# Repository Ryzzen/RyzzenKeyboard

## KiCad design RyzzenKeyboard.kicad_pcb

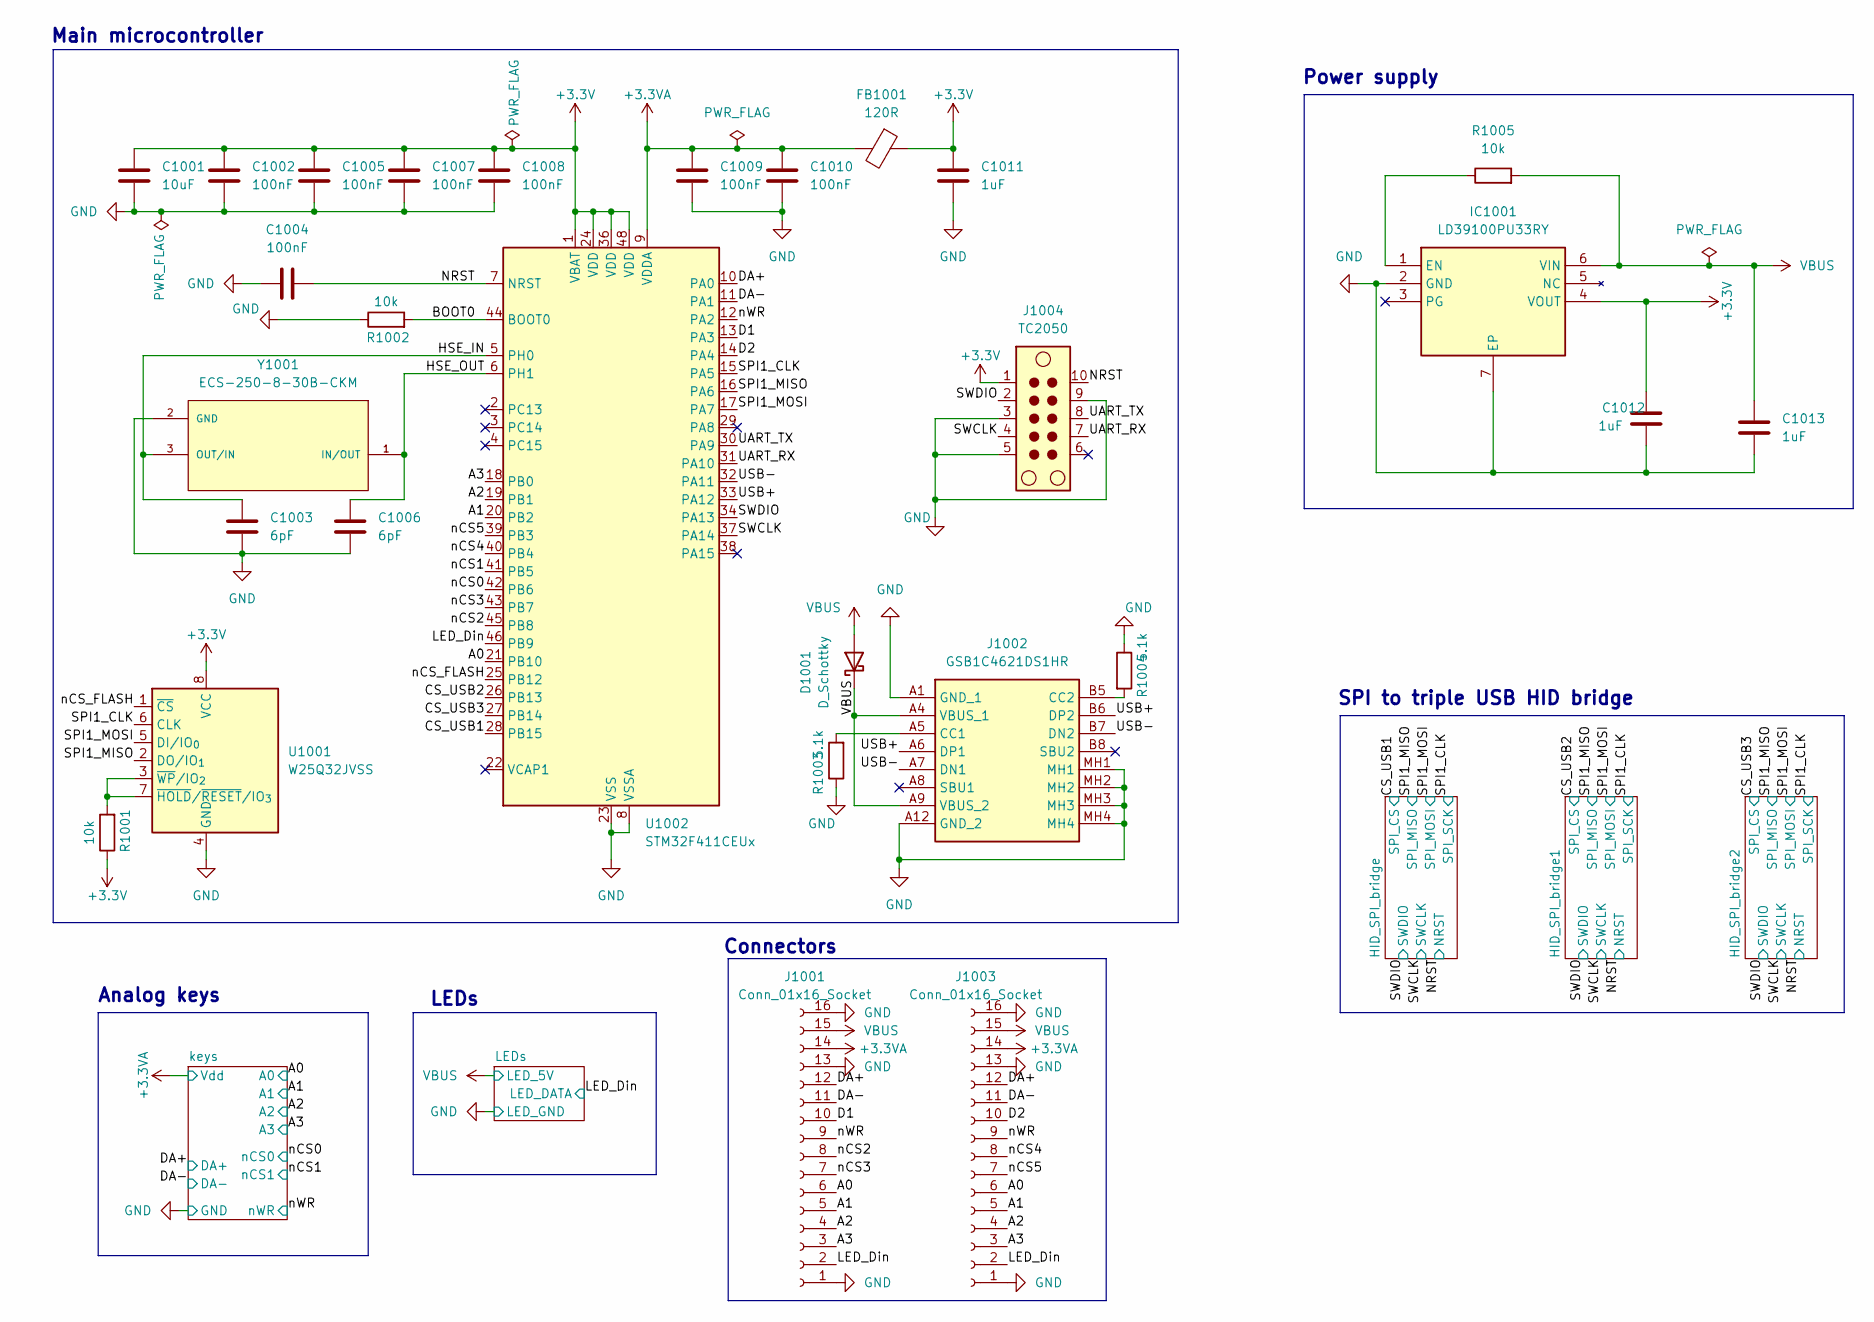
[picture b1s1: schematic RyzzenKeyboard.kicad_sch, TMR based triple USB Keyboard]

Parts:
C1001: 10uF; C_0603_1608Metric_Pad1.08x0.95mm_HandSolder
C1002, C1004, C1005, C1007, C1008, C1009, C1010: 100nF; C_0603_1608Metric_Pad1.08x0.95mm_HandSolder
C1003, C1006: 6pF; C_0603_1608Metric_Pad1.08x0.95mm_HandSolder
C1011, C1012, C1013: 1uF; C_0603_1608Metric_Pad1.08x0.95mm_HandSolder
D1001: D_Schottky; CUHS20S40H3F
FB1001: 120R; BLM21AG102BH1J
IC1001: LD39100PU33RY; SON95P300X300X90-7N-D; Mouser Part Number 511-LD39100PU33RY
J1001, J1003: Conn_01x16_Socket; JST_XH_S16B-XH-A_1x16_P2.50mm_Horizontal
J1002: GSB1C4621DS1HR; Manufacturer_Part_Number GSB1C4621DS1HR
J1004: TC2050; Tag-Connect_TC2050-IDC-NL_2x05_P1.27mm_Vertical
R1001, R1002, R1005: 10k; R_0603_1608Metric_Pad0.98x0.95mm_HandSolder
R1003, R1004: 5.1k; R_0603_1608Metric_Pad0.98x0.95mm_HandSolder
U1001: W25Q32JVSS; SOIC-8_5.3x5.3mm_P1.27mm
U1002: STM32F411CEUx; QFN-48-1EP_7x7mm_P0.5mm_EP5.6x5.6mm
Y1001: ECS-250-8-30B-CKM; XTAL_ECS-250-8-30B-CKM

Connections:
+3.3V: C1001.1, C1002.1, C1005.1, C1007.1, C1008.1, C1011.1, C1012.1, FB1001.1, IC1001.4 (VOUT), J1004.1, R1001.1, U1001.8 (VCC), U1002.1 (VBAT), U1002.24 (VDD), U1002.36 (VDD), U1002.48 (VDD); also elsewhere on the board
+3.3VA: C1009.1, C1010.1, FB1001.2, J1001.14, J1003.14, U1002.9 (VDDA); also elsewhere on the board
/A0: J1001.6, J1003.6, U1002.21 (PB10); also elsewhere on the board
/A1: J1001.5, J1003.5, U1002.20 (PB2); also elsewhere on the board
/A2: J1001.4, J1003.4, U1002.19 (PB1); also elsewhere on the board
/A3: J1001.3, J1003.3, U1002.18 (PB0); also elsewhere on the board
/BOOT0: R1002.2, U1002.44 (BOOT0)
/CS_USB1: U1002.28 (PB15); also elsewhere on the board
/CS_USB2: U1002.26 (PB13); also elsewhere on the board
/CS_USB3: U1002.27 (PB14); also elsewhere on the board
/D1: J1001.10, U1002.13 (PA3)
/D2: J1003.10, U1002.14 (PA4)
/DA+: J1001.12, J1003.12, U1002.10 (PA0); also elsewhere on the board
/DA-: J1001.11, J1003.11, U1002.11 (PA1); also elsewhere on the board
/HSE_IN: C1003.1, U1002.5 (PH0), Y1001.3 (OUT/IN)
/HSE_OUT: C1006.1, U1002.6 (PH1), Y1001.1 (IN/OUT)
/LED_Din: J1001.2, J1003.2, U1002.46 (PB9); also elsewhere on the board
/NRST: C1004.1, J1004.10, U1002.7 (NRST); also elsewhere on the board
/SPI1_CLK: U1001.6 (CLK), U1002.15 (PA5); also elsewhere on the board
/SPI1_MISO: U1001.2 (DO/IO_{1}), U1002.16 (PA6); also elsewhere on the board
/SPI1_MOSI: U1001.5 (DI/IO_{0}), U1002.17 (PA7); also elsewhere on the board
/SWCLK: J1004.4, U1002.37 (PA14); also elsewhere on the board
/SWDIO: J1004.2, U1002.34 (PA13); also elsewhere on the board
/UART_RX: J1004.7, U1002.31 (PA10)
/UART_TX: J1004.8, U1002.30 (PA9)
/USB+: J1002.A6 (DP1), J1002.B6 (DP2), U1002.33 (PA12)
/USB-: J1002.A7 (DN1), J1002.B7 (DN2), U1002.32 (PA11)
/nCS0: U1002.42 (PB6); also elsewhere on the board
/nCS1: U1002.41 (PB5); also elsewhere on the board
/nCS2: J1001.8, U1002.45 (PB8)
/nCS3: J1001.7, U1002.43 (PB7)
/nCS4: J1003.8, U1002.40 (PB4)
/nCS5: J1003.7, U1002.39 (PB3)
/nCS_FLASH: U1001.1 (~CS), U1002.25 (PB12)
/nWR: J1001.9, J1003.9, U1002.12 (PA2); also elsewhere on the board
GND: C1001.2, C1002.2, C1003.2, C1004.2, C1005.2, C1006.2, C1007.2, C1008.2, C1009.2, C1010.2, C1011.2, C1012.2, C1013.2, IC1001.2 (GND), IC1001.7 (EP), J1001.1, J1001.13, J1001.16, J1002.A1 (GND_1), J1002.A12 (GND_2), J1002.MH1, J1002.MH2, J1002.MH3, J1002.MH4, J1003.1, J1003.13, J1003.16, J1004.3, J1004.5, J1004.9, R1002.1, R1003.1, R1004.1, U1001.4 (GND), U1002.8 (VSSA), U1002.23 (VSS), U1002.35 (VSS), U1002.47 (VSS), U1002.49 (VSS), Y1001.2 (GND), Y1001.4 (GND); also elsewhere on the board
unnamed: IC1001.1 (EN), R1005.1
unnamed: J1002.A5 (CC1), R1003.2
unnamed: J1002.B5 (CC2), R1004.2
unnamed: R1001.2, U1001.3 (~WP/IO_{2}), U1001.7 (~HOLD/~RESET/IO_{3})
VBUS: C1013.1, D1001.1 (K), D1001.2 (A), IC1001.6 (VIN), J1001.15, J1002.A4 (VBUS_1), J1002.A9 (VBUS_2), J1003.15, R1005.2; also elsewhere on the board

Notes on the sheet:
Main microcontroller
Power supply
LEDs
Connectors
Analog keys
SPI to triple USB HID bridge

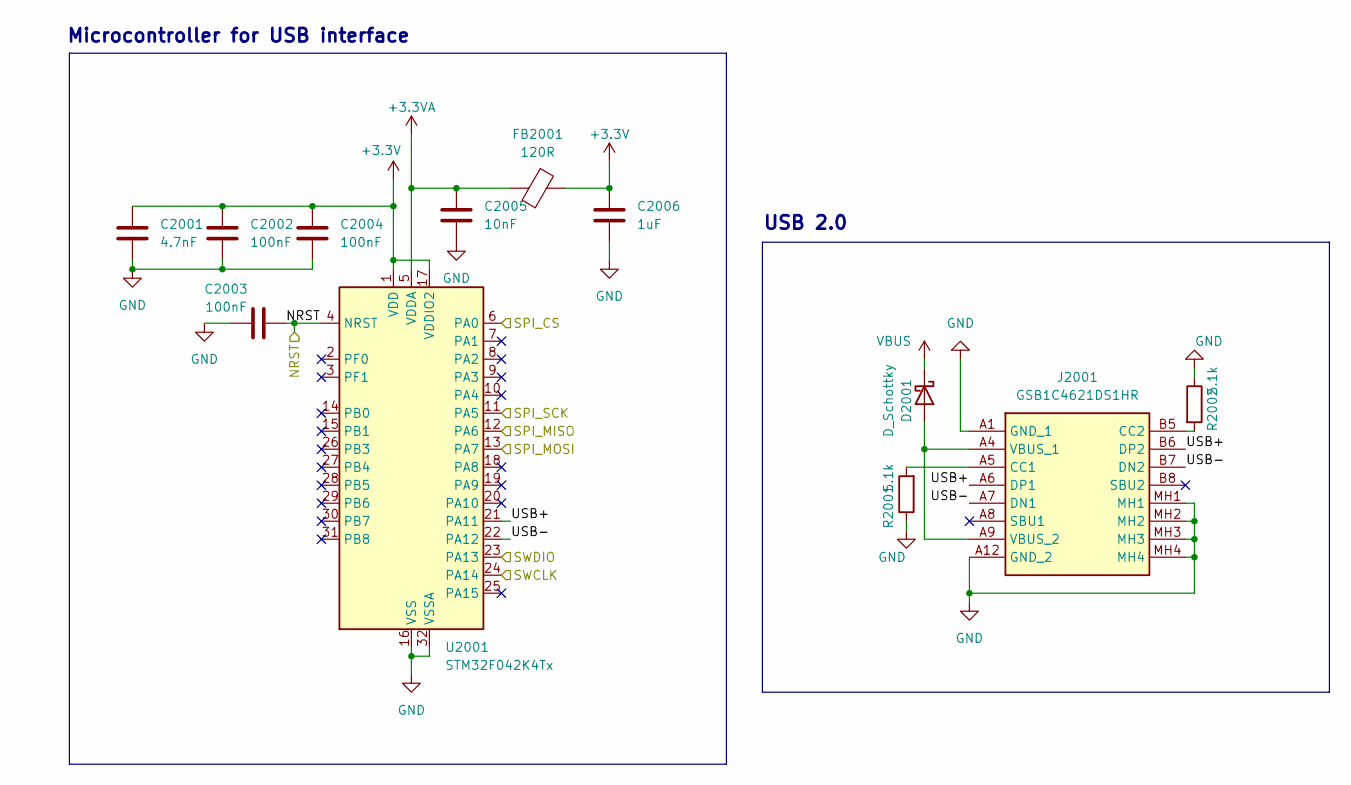
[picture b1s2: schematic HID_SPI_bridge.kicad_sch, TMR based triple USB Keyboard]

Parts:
C2001: 4.7nF; C_0603_1608Metric_Pad1.08x0.95mm_HandSolder
C2002, C2003, C2004: 100nF; C_0603_1608Metric_Pad1.08x0.95mm_HandSolder
C2005: 10nF; C_0603_1608Metric_Pad1.08x0.95mm_HandSolder
C2006: 1uF; C_0603_1608Metric_Pad1.08x0.95mm_HandSolder
D2001: D_Schottky; CUHS20S40H3F
FB2001: 120R; BLM21AG102BH1J
J2001: GSB1C4621DS1HR; Manufacturer_Part_Number GSB1C4621DS1HR
R2001, R2002: 5.1k; R_0603_1608Metric_Pad0.98x0.95mm_HandSolder
U2001: STM32F042K4Tx; LQFP-32_7x7mm_P0.8mm

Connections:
+3.3V: C2001.1, C2002.1, C2004.1, C2006.1, FB2001.1, U2001.1 (VDD), U2001.17 (VDDIO2); also elsewhere on the board
+3.3VA: C2005.1, FB2001.2, U2001.5 (VDDA); also elsewhere on the board
/CS_USB1: U2001.6 (PA0); also elsewhere on the board
/HID_SPI_bridge/USB+: J2001.A6 (DP1), J2001.B6 (DP2), U2001.21 (PA11)
/HID_SPI_bridge/USB-: J2001.A7 (DN1), J2001.B7 (DN2), U2001.22 (PA12)
/NRST: C2003.2, U2001.4 (NRST); also elsewhere on the board
/SPI1_CLK: U2001.11 (PA5); also elsewhere on the board
/SPI1_MISO: U2001.12 (PA6); also elsewhere on the board
/SPI1_MOSI: U2001.13 (PA7); also elsewhere on the board
/SWCLK: U2001.24 (PA14); also elsewhere on the board
/SWDIO: U2001.23 (PA13); also elsewhere on the board
GND: C2001.2, C2002.2, C2003.1, C2004.2, C2005.2, C2006.2, J2001.A1 (GND_1), J2001.A12 (GND_2), J2001.MH1, J2001.MH2, J2001.MH3, J2001.MH4, R2001.1, R2002.1, U2001.16 (VSS), U2001.32 (VSSA); also elsewhere on the board
unnamed: D2001.2 (A), J2001.A4 (VBUS_1), J2001.A9 (VBUS_2)
unnamed: J2001.A5 (CC1), R2001.2
unnamed: J2001.B5 (CC2), R2002.2
VBUS: D2001.1 (K); also elsewhere on the board

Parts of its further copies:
C207001, C208001: 4.7nF; C_0603_1608Metric_Pad1.08x0.95mm_HandSolder
C207002, C207003, C207004, C208002, C208003, C208004: 100nF; C_0603_1608Metric_Pad1.08x0.95mm_HandSolder
C207005, C208005: 10nF; C_0603_1608Metric_Pad1.08x0.95mm_HandSolder
C207006, C208006: 1uF; C_0603_1608Metric_Pad1.08x0.95mm_HandSolder
D207001, D208001: D_Schottky; CUHS20S40H3F
FB207001, FB208001: 120R; BLM21AG102BH1J
J207001, J208001: GSB1C4621DS1HR; Manufacturer_Part_Number GSB1C4621DS1HR
R207001, R207002, R208001, R208002: 5.1k; R_0603_1608Metric_Pad0.98x0.95mm_HandSolder
U207001, U208001: STM32F042K4Tx; LQFP-32_7x7mm_P0.8mm

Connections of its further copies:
+3.3V: C207001.1, C207002.1, C207004.1, C207006.1, C208001.1, C208002.1, C208004.1, C208006.1, FB207001.1, FB208001.1, U207001.1 (VDD), U207001.17 (VDDIO2), U208001.1 (VDD), U208001.17 (VDDIO2); also elsewhere on the board
+3.3VA: C207005.1, C208005.1, FB207001.2, FB208001.2, U207001.5 (VDDA), U208001.5 (VDDA); also elsewhere on the board
/CS_USB2: U208001.6 (PA0); also elsewhere on the board
/CS_USB3: U207001.6 (PA0); also elsewhere on the board
/HID_SPI_bridge1/USB+: J208001.A6 (DP1), J208001.B6 (DP2), U208001.21 (PA11)
/HID_SPI_bridge1/USB-: J208001.A7 (DN1), J208001.B7 (DN2), U208001.22 (PA12)
/HID_SPI_bridge2/USB+: J207001.A6 (DP1), J207001.B6 (DP2), U207001.21 (PA11)
/HID_SPI_bridge2/USB-: J207001.A7 (DN1), J207001.B7 (DN2), U207001.22 (PA12)
/NRST: C207003.2, C208003.2, U207001.4 (NRST), U208001.4 (NRST); also elsewhere on the board
/SPI1_CLK: U207001.11 (PA5), U208001.11 (PA5); also elsewhere on the board
/SPI1_MISO: U207001.12 (PA6), U208001.12 (PA6); also elsewhere on the board
/SPI1_MOSI: U207001.13 (PA7), U208001.13 (PA7); also elsewhere on the board
/SWCLK: U207001.24 (PA14), U208001.24 (PA14); also elsewhere on the board
/SWDIO: U207001.23 (PA13), U208001.23 (PA13); also elsewhere on the board
GND: C207001.2, C207002.2, C207003.1, C207004.2, C207005.2, C207006.2, C208001.2, C208002.2, C208003.1, C208004.2, C208005.2, C208006.2, J207001.A1 (GND_1), J207001.A12 (GND_2), J207001.MH1, J207001.MH2, J207001.MH3, J207001.MH4, J208001.A1 (GND_1), J208001.A12 (GND_2), J208001.MH1, J208001.MH2, J208001.MH3, J208001.MH4, R207001.1, R207002.1, R208001.1, R208002.1, U207001.16 (VSS), U207001.32 (VSSA), U208001.16 (VSS), U208001.32 (VSSA); also elsewhere on the board
unnamed: D207001.2 (A), J207001.A4 (VBUS_1), J207001.A9 (VBUS_2)
unnamed: D208001.2 (A), J208001.A4 (VBUS_1), J208001.A9 (VBUS_2)
unnamed: J207001.A5 (CC1), R207001.2
unnamed: J207001.B5 (CC2), R207002.2
unnamed: J208001.A5 (CC1), R208001.2
unnamed: J208001.B5 (CC2), R208002.2
VBUS: D207001.1 (K), D208001.1 (K); also elsewhere on the board

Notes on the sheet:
Microcontroller for USB interface
USB 2.0

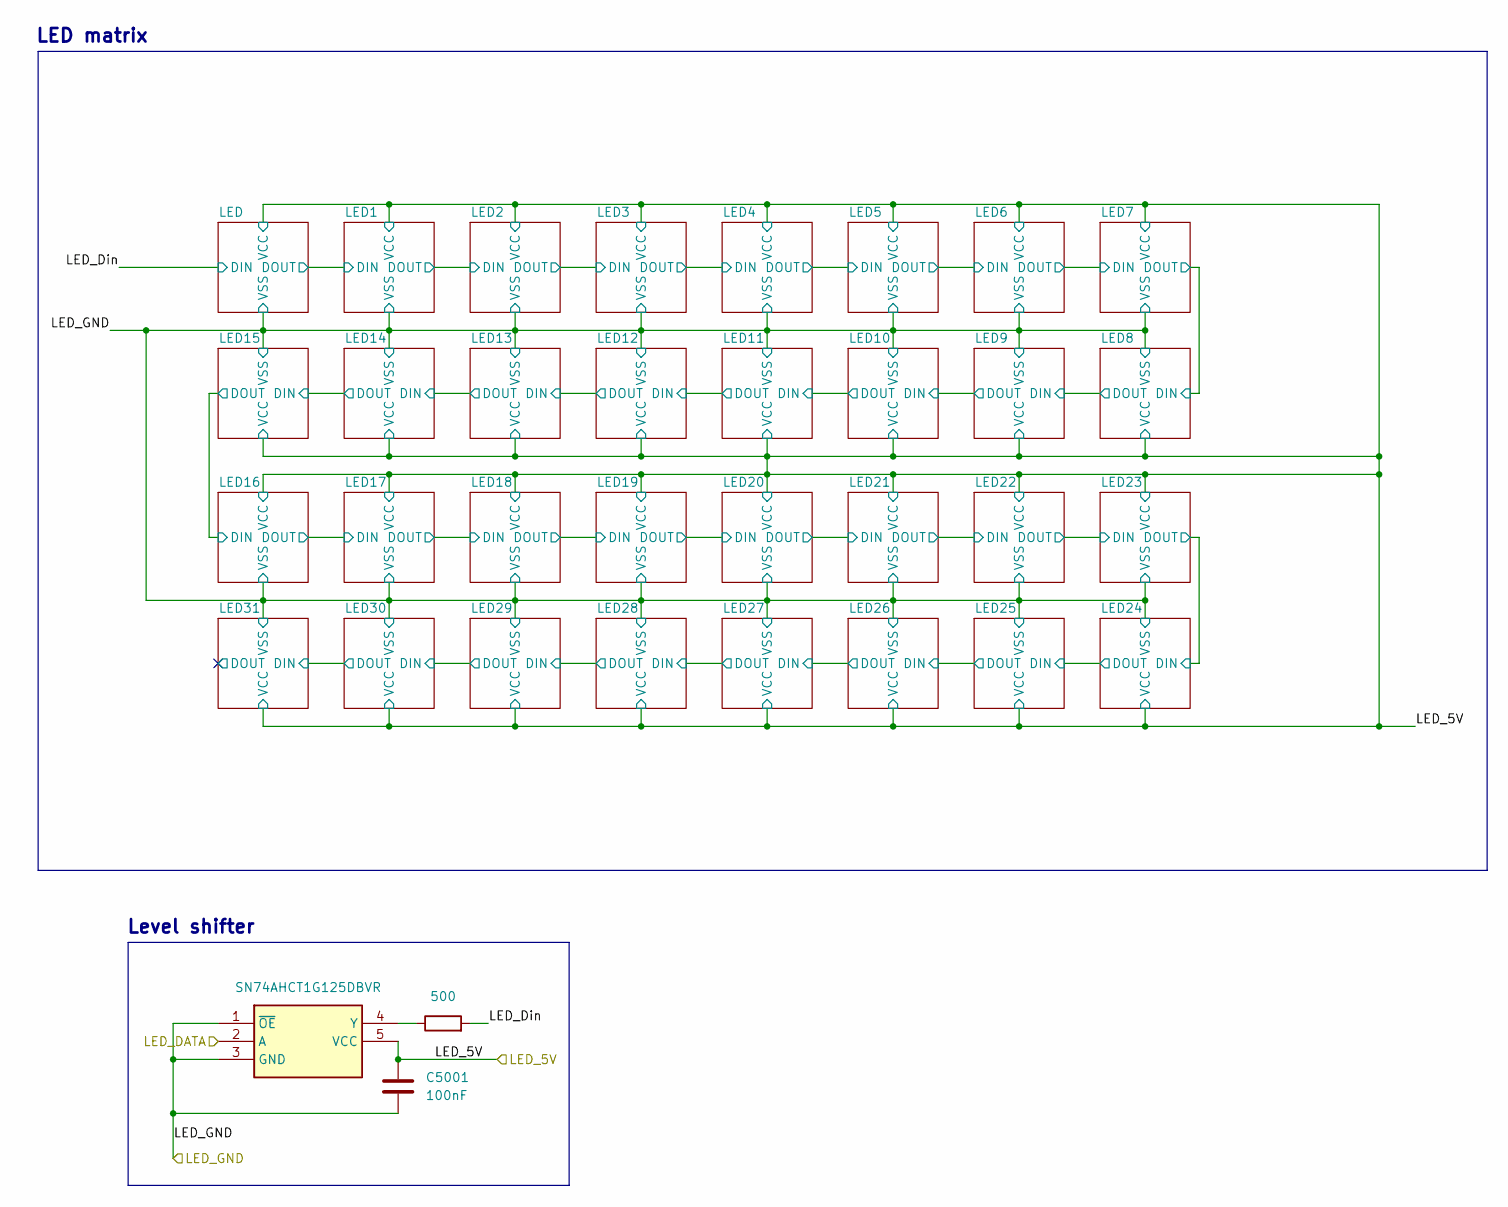
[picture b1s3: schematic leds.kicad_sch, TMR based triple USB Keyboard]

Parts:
C5001: 100nF; C_0603_1608Metric_Pad1.08x0.95mm_HandSolder
IC5001: SN74AHCT1G125DBVR; SOT95P280X145-5N; Mouser Part Number 595-SNAHCT1G125DBVR
R5001: 500; R_0603_1608Metric_Pad0.98x0.95mm_HandSolder

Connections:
/LED_Din: IC5001.2 (A); also elsewhere on the board
/LEDs/LED_Din: R5001.2; also elsewhere on the board
GND: C5001.1, IC5001.1 (~OE), IC5001.3 (GND); also elsewhere on the board
unnamed: IC5001.4 (Y), R5001.1
VBUS: C5001.2, IC5001.5 (VCC); also elsewhere on the board

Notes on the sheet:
LED matrix
Level shifter

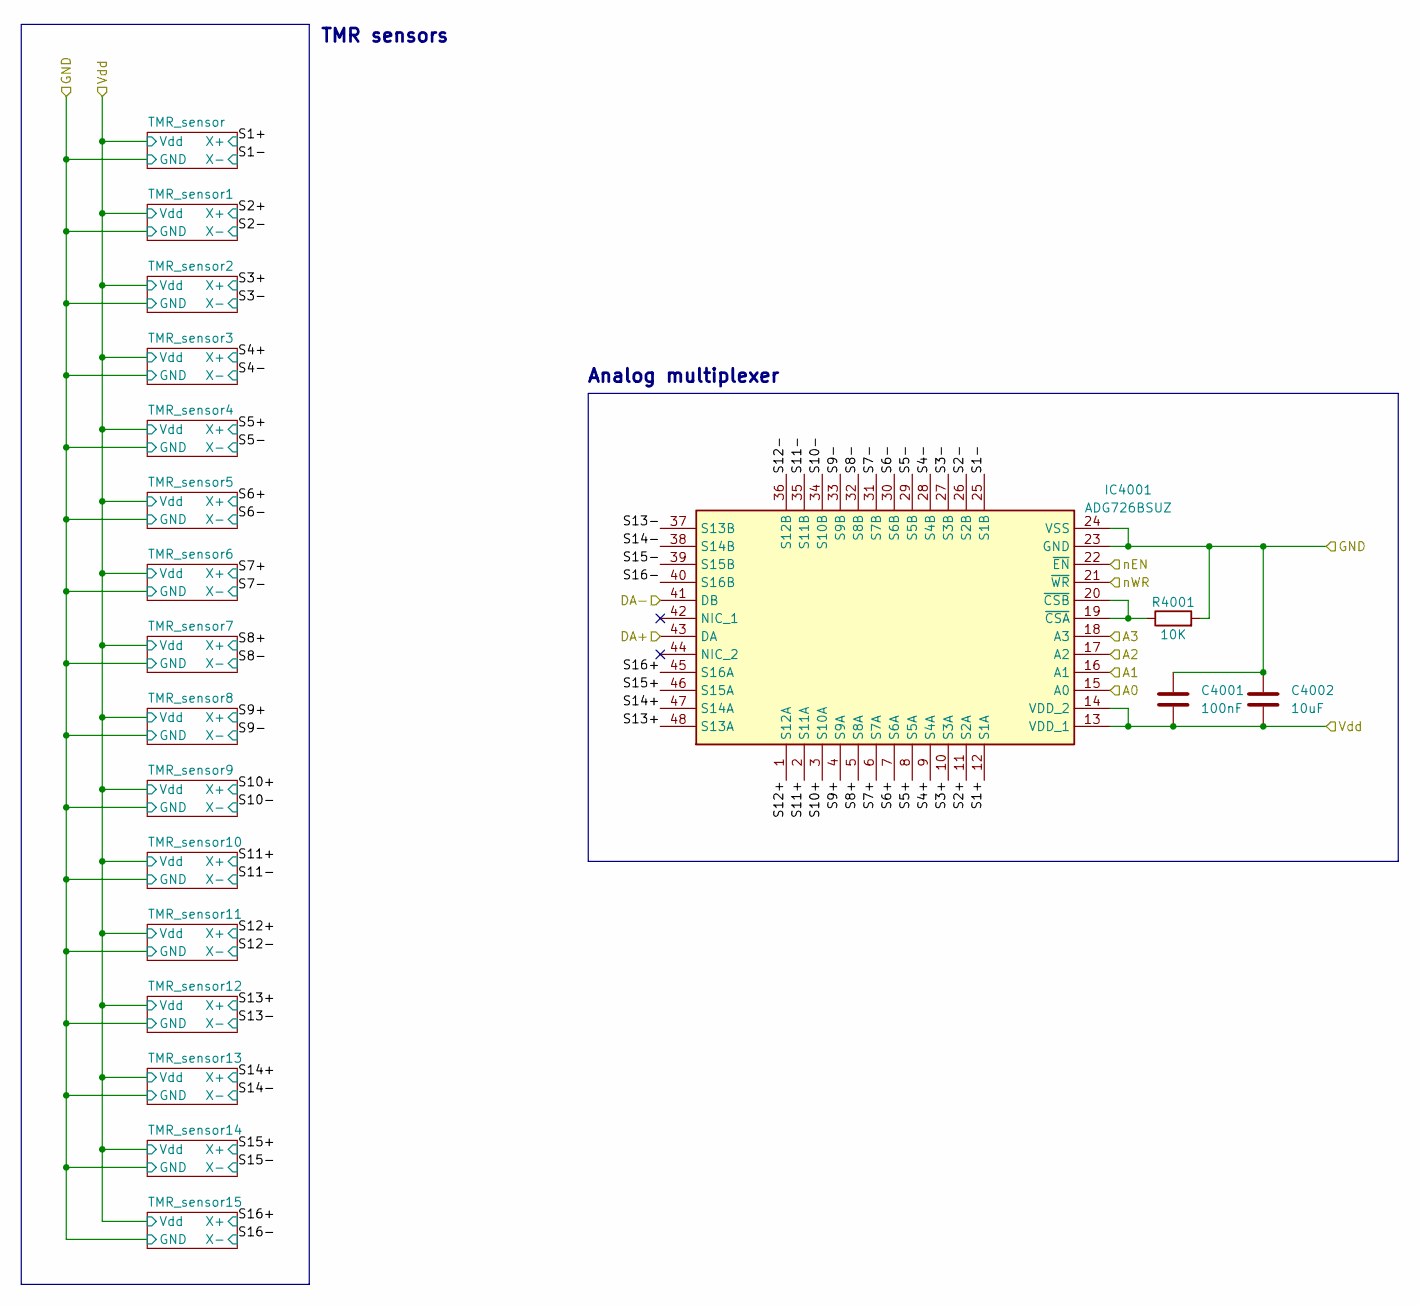
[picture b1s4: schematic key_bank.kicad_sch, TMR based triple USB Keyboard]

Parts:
C4001: 100nF; C_0603_1608Metric_Pad1.08x0.95mm_HandSolder
C4002: 10uF; C_0603_1608Metric_Pad1.08x0.95mm_HandSolder
IC4001: ADG726BSUZ; QFP50P900X900X120-48N; Mouser Part Number 584-ADG726BSUZ
R4001: 10K; R_0603_1608Metric_Pad0.98x0.95mm_HandSolder

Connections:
+3.3VA: C4001.2, C4002.2, IC4001.13 (VDD_1), IC4001.14 (VDD_2); also elsewhere on the board
/A0: IC4001.15 (A0); also elsewhere on the board
/A1: IC4001.16 (A1); also elsewhere on the board
/A2: IC4001.17 (A2); also elsewhere on the board
/A3: IC4001.18 (A3); also elsewhere on the board
/DA+: IC4001.43 (DA); also elsewhere on the board
/DA-: IC4001.41 (DB); also elsewhere on the board
/keys/key_bank2/S1+: IC4001.12 (S1A); also elsewhere on the board
/keys/key_bank2/S1-: IC4001.25 (S1B); also elsewhere on the board
/keys/key_bank2/S2+: IC4001.11 (S2A); also elsewhere on the board
/keys/key_bank2/S2-: IC4001.26 (S2B); also elsewhere on the board
/keys/key_bank2/S3+: IC4001.10 (S3A); also elsewhere on the board
/keys/key_bank2/S3-: IC4001.27 (S3B); also elsewhere on the board
/keys/key_bank2/S4+: IC4001.9 (S4A); also elsewhere on the board
/keys/key_bank2/S4-: IC4001.28 (S4B); also elsewhere on the board
/keys/key_bank2/S5+: IC4001.8 (S5A); also elsewhere on the board
/keys/key_bank2/S5-: IC4001.29 (S5B); also elsewhere on the board
/keys/key_bank2/S6+: IC4001.7 (S6A); also elsewhere on the board
/keys/key_bank2/S6-: IC4001.30 (S6B); also elsewhere on the board
/keys/key_bank2/S7+: IC4001.6 (S7A); also elsewhere on the board
/keys/key_bank2/S7-: IC4001.31 (S7B); also elsewhere on the board
/keys/key_bank2/S8+: IC4001.5 (S8A); also elsewhere on the board
/keys/key_bank2/S8-: IC4001.32 (S8B); also elsewhere on the board
/keys/key_bank2/S9+: IC4001.4 (S9A); also elsewhere on the board
/keys/key_bank2/S9-: IC4001.33 (S9B); also elsewhere on the board
/keys/key_bank2/S10+: IC4001.3 (S10A); also elsewhere on the board
/keys/key_bank2/S10-: IC4001.34 (S10B); also elsewhere on the board
/keys/key_bank2/S11+: IC4001.2 (S11A); also elsewhere on the board
/keys/key_bank2/S11-: IC4001.35 (S11B); also elsewhere on the board
/keys/key_bank2/S12+: IC4001.1 (S12A); also elsewhere on the board
/keys/key_bank2/S12-: IC4001.36 (S12B); also elsewhere on the board
/keys/key_bank2/S13+: IC4001.48 (S13A); also elsewhere on the board
/keys/key_bank2/S13-: IC4001.37 (S13B); also elsewhere on the board
/keys/key_bank2/S14+: IC4001.47 (S14A); also elsewhere on the board
/keys/key_bank2/S14-: IC4001.38 (S14B); also elsewhere on the board
/keys/key_bank2/S15+: IC4001.46 (S15A); also elsewhere on the board
/keys/key_bank2/S15-: IC4001.39 (S15B); also elsewhere on the board
/keys/key_bank2/S16+: IC4001.45 (S16A); also elsewhere on the board
/keys/key_bank2/S16-: IC4001.40 (S16B); also elsewhere on the board
/nCS0: IC4001.22 (~EN); also elsewhere on the board
/nWR: IC4001.21 (~WR); also elsewhere on the board
GND: C4001.1, C4002.1, IC4001.23 (GND), IC4001.24 (VSS), R4001.2; also elsewhere on the board
unnamed: IC4001.19 (~CSA), IC4001.20 (~CSB), R4001.1

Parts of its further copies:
C204001: 100nF; C_0603_1608Metric_Pad1.08x0.95mm_HandSolder
C204002: 10uF; C_0603_1608Metric_Pad1.08x0.95mm_HandSolder
IC204001: ADG726BSUZ; QFP50P900X900X120-48N; Mouser Part Number 584-ADG726BSUZ
R204001: 10K; R_0603_1608Metric_Pad0.98x0.95mm_HandSolder

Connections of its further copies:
+3.3VA: C204001.2, C204002.2, IC204001.13 (VDD_1), IC204001.14 (VDD_2); also elsewhere on the board
/A0: IC204001.15 (A0); also elsewhere on the board
/A1: IC204001.16 (A1); also elsewhere on the board
/A2: IC204001.17 (A2); also elsewhere on the board
/A3: IC204001.18 (A3); also elsewhere on the board
/DA+: IC204001.43 (DA); also elsewhere on the board
/DA-: IC204001.41 (DB); also elsewhere on the board
/keys/key_bank3/S1+: IC204001.12 (S1A); also elsewhere on the board
/keys/key_bank3/S1-: IC204001.25 (S1B); also elsewhere on the board
/keys/key_bank3/S2+: IC204001.11 (S2A); also elsewhere on the board
/keys/key_bank3/S2-: IC204001.26 (S2B); also elsewhere on the board
/keys/key_bank3/S3+: IC204001.10 (S3A); also elsewhere on the board
/keys/key_bank3/S3-: IC204001.27 (S3B); also elsewhere on the board
/keys/key_bank3/S4+: IC204001.9 (S4A); also elsewhere on the board
/keys/key_bank3/S4-: IC204001.28 (S4B); also elsewhere on the board
/keys/key_bank3/S5+: IC204001.8 (S5A); also elsewhere on the board
/keys/key_bank3/S5-: IC204001.29 (S5B); also elsewhere on the board
/keys/key_bank3/S6+: IC204001.7 (S6A); also elsewhere on the board
/keys/key_bank3/S6-: IC204001.30 (S6B); also elsewhere on the board
/keys/key_bank3/S7+: IC204001.6 (S7A); also elsewhere on the board
/keys/key_bank3/S7-: IC204001.31 (S7B); also elsewhere on the board
/keys/key_bank3/S8+: IC204001.5 (S8A); also elsewhere on the board
/keys/key_bank3/S8-: IC204001.32 (S8B); also elsewhere on the board
/keys/key_bank3/S9+: IC204001.4 (S9A); also elsewhere on the board
/keys/key_bank3/S9-: IC204001.33 (S9B); also elsewhere on the board
/keys/key_bank3/S10+: IC204001.3 (S10A); also elsewhere on the board
/keys/key_bank3/S10-: IC204001.34 (S10B); also elsewhere on the board
/keys/key_bank3/S11+: IC204001.2 (S11A); also elsewhere on the board
/keys/key_bank3/S11-: IC204001.35 (S11B); also elsewhere on the board
/keys/key_bank3/S12+: IC204001.1 (S12A); also elsewhere on the board
/keys/key_bank3/S12-: IC204001.36 (S12B); also elsewhere on the board
/keys/key_bank3/S13+: IC204001.48 (S13A); also elsewhere on the board
/keys/key_bank3/S13-: IC204001.37 (S13B); also elsewhere on the board
/keys/key_bank3/S14+: IC204001.47 (S14A); also elsewhere on the board
/keys/key_bank3/S14-: IC204001.38 (S14B); also elsewhere on the board
/keys/key_bank3/S15+: IC204001.46 (S15A); also elsewhere on the board
/keys/key_bank3/S15-: IC204001.39 (S15B); also elsewhere on the board
/keys/key_bank3/S16+: IC204001.45 (S16A); also elsewhere on the board
/keys/key_bank3/S16-: IC204001.40 (S16B); also elsewhere on the board
/nCS1: IC204001.22 (~EN); also elsewhere on the board
/nWR: IC204001.21 (~WR); also elsewhere on the board
GND: C204001.1, C204002.1, IC204001.23 (GND), IC204001.24 (VSS), R204001.2; also elsewhere on the board
unnamed: IC204001.19 (~CSA), IC204001.20 (~CSB), R204001.1

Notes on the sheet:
TMR sensors
Analog multiplexer

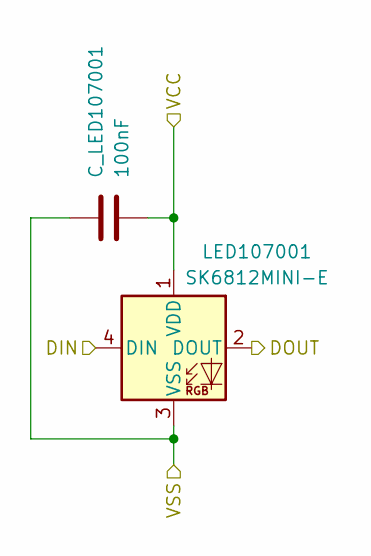
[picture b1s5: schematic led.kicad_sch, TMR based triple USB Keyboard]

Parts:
C_LED107001: 100nF; C_0603_1608Metric_Pad1.08x0.95mm_HandSolder
LED107001: SK6812MINI-E; MX_SK6812MINI-E_REV

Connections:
/LEDs/LED/DOUT: LED107001.2 (DOUT); also elsewhere on the board
/LEDs/LED_Din: LED107001.4 (DIN); also elsewhere on the board
GND: C_LED107001.2, LED107001.3 (VSS); also elsewhere on the board
VBUS: C_LED107001.1, LED107001.1 (VDD); also elsewhere on the board

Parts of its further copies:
C_LED108001, C_LED109001, C_LED110001, C_LED111001, C_LED112001, C_LED113001, C_LED114001, C_LED115001, C_LED116001, C_LED117001, C_LED118001, C_LED119001, C_LED120001, C_LED121001, C_LED122001, C_LED123001, C_LED124001, C_LED125001, C_LED126001, C_LED127001, C_LED128001, C_LED129001, C_LED130001, C_LED131001, C_LED132001, C_LED133001, C_LED134001, C_LED135001, C_LED136001, C_LED137001, C_LED138001: 100nF; C_0603_1608Metric_Pad1.08x0.95mm_HandSolder
LED108001, LED109001, LED110001, LED111001, LED112001, LED113001, LED114001, LED115001, LED116001, LED117001, LED118001, LED119001, LED120001, LED121001, LED122001, LED123001, LED124001, LED125001, LED126001, LED127001, LED128001, LED129001, LED130001, LED131001, LED132001, LED133001, LED134001, LED135001, LED136001, LED137001, LED138001: SK6812MINI-E; MX_SK6812MINI-E_REV

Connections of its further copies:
/LEDs/LED1/DOUT: LED108001.2 (DOUT), LED109001.4 (DIN)
/LEDs/LED2/DOUT: LED109001.2 (DOUT), LED110001.4 (DIN)
/LEDs/LED3/DOUT: LED110001.2 (DOUT), LED111001.4 (DIN)
/LEDs/LED4/DOUT: LED111001.2 (DOUT), LED112001.4 (DIN)
/LEDs/LED5/DOUT: LED112001.2 (DOUT), LED113001.4 (DIN)
/LEDs/LED6/DOUT: LED113001.2 (DOUT), LED114001.4 (DIN)
/LEDs/LED7/DOUT: LED114001.2 (DOUT), LED115001.4 (DIN)
/LEDs/LED8/DOUT: LED115001.2 (DOUT), LED116001.4 (DIN)
/LEDs/LED10/DIN: LED116001.2 (DOUT), LED117001.4 (DIN)
/LEDs/LED10/DOUT: LED117001.2 (DOUT), LED118001.4 (DIN)
/LEDs/LED11/DOUT: LED118001.2 (DOUT), LED119001.4 (DIN)
/LEDs/LED12/DOUT: LED119001.2 (DOUT), LED120001.4 (DIN)
/LEDs/LED13/DOUT: LED120001.2 (DOUT), LED121001.4 (DIN)
/LEDs/LED14/DOUT: LED121001.2 (DOUT), LED122001.4 (DIN)
/LEDs/LED15/DOUT: LED122001.2 (DOUT), LED123001.4 (DIN)
/LEDs/LED16/DOUT: LED123001.2 (DOUT), LED124001.4 (DIN)
/LEDs/LED17/DOUT: LED124001.2 (DOUT), LED125001.4 (DIN)
/LEDs/LED18/DOUT: LED125001.2 (DOUT), LED126001.4 (DIN)
/LEDs/LED19/DOUT: LED126001.2 (DOUT), LED127001.4 (DIN)
/LEDs/LED20/DOUT: LED127001.2 (DOUT), LED128001.4 (DIN)
/LEDs/LED21/DOUT: LED128001.2 (DOUT), LED129001.4 (DIN)
/LEDs/LED22/DOUT: LED129001.2 (DOUT), LED130001.4 (DIN)
/LEDs/LED23/DOUT: LED130001.2 (DOUT), LED131001.4 (DIN)
/LEDs/LED24/DOUT: LED131001.2 (DOUT), LED132001.4 (DIN)
/LEDs/LED25/DOUT: LED132001.2 (DOUT), LED133001.4 (DIN)
/LEDs/LED26/DOUT: LED133001.2 (DOUT), LED134001.4 (DIN)
/LEDs/LED27/DOUT: LED134001.2 (DOUT), LED135001.4 (DIN)
/LEDs/LED28/DOUT: LED135001.2 (DOUT), LED136001.4 (DIN)
/LEDs/LED29/DOUT: LED136001.2 (DOUT), LED137001.4 (DIN)
/LEDs/LED30/DOUT: LED137001.2 (DOUT), LED138001.4 (DIN)
/LEDs/LED31/DOUT: LED138001.2 (DOUT)
/LEDs/LED/DOUT: LED108001.4 (DIN); also elsewhere on the board
GND: C_LED108001.2, C_LED109001.2, C_LED110001.2, C_LED111001.2, C_LED112001.2, C_LED113001.2, C_LED114001.2, C_LED115001.2, C_LED116001.2, C_LED117001.2, C_LED118001.2, C_LED119001.2, C_LED120001.2, C_LED121001.2, C_LED122001.2, C_LED123001.2, C_LED124001.2, C_LED125001.2, C_LED126001.2, C_LED127001.2, C_LED128001.2, C_LED129001.2, C_LED130001.2, C_LED131001.2, C_LED132001.2, C_LED133001.2, C_LED134001.2, C_LED135001.2, C_LED136001.2, C_LED137001.2, C_LED138001.2, LED108001.3 (VSS), LED109001.3 (VSS), LED110001.3 (VSS), LED111001.3 (VSS), LED112001.3 (VSS), LED113001.3 (VSS), LED114001.3 (VSS), LED115001.3 (VSS), LED116001.3 (VSS), LED117001.3 (VSS), LED118001.3 (VSS), LED119001.3 (VSS), LED120001.3 (VSS), LED121001.3 (VSS), LED122001.3 (VSS), LED123001.3 (VSS), LED124001.3 (VSS), LED125001.3 (VSS), LED126001.3 (VSS), LED127001.3 (VSS), LED128001.3 (VSS), LED129001.3 (VSS), LED130001.3 (VSS), LED131001.3 (VSS), LED132001.3 (VSS), LED133001.3 (VSS), LED134001.3 (VSS), LED135001.3 (VSS), LED136001.3 (VSS), LED137001.3 (VSS), LED138001.3 (VSS); also elsewhere on the board
VBUS: C_LED108001.1, C_LED109001.1, C_LED110001.1, C_LED111001.1, C_LED112001.1, C_LED113001.1, C_LED114001.1, C_LED115001.1, C_LED116001.1, C_LED117001.1, C_LED118001.1, C_LED119001.1, C_LED120001.1, C_LED121001.1, C_LED122001.1, C_LED123001.1, C_LED124001.1, C_LED125001.1, C_LED126001.1, C_LED127001.1, C_LED128001.1, C_LED129001.1, C_LED130001.1, C_LED131001.1, C_LED132001.1, C_LED133001.1, C_LED134001.1, C_LED135001.1, C_LED136001.1, C_LED137001.1, C_LED138001.1, LED108001.1 (VDD), LED109001.1 (VDD), LED110001.1 (VDD), LED111001.1 (VDD), LED112001.1 (VDD), LED113001.1 (VDD), LED114001.1 (VDD), LED115001.1 (VDD), LED116001.1 (VDD), LED117001.1 (VDD), LED118001.1 (VDD), LED119001.1 (VDD), LED120001.1 (VDD), LED121001.1 (VDD), LED122001.1 (VDD), LED123001.1 (VDD), LED124001.1 (VDD), LED125001.1 (VDD), LED126001.1 (VDD), LED127001.1 (VDD), LED128001.1 (VDD), LED129001.1 (VDD), LED130001.1 (VDD), LED131001.1 (VDD), LED132001.1 (VDD), LED133001.1 (VDD), LED134001.1 (VDD), LED135001.1 (VDD), LED136001.1 (VDD), LED137001.1 (VDD), LED138001.1 (VDD); also elsewhere on the board
